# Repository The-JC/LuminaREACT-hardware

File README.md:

# LuminaREACT - Hardware
This repository is the hardware documentation of the LuminaREACT project.

LuminaREACT is CORTEX-M4 based audio visualizer for LED strips using the WS2812 led chip.
For further information visit: [LuminaREACT Firmware](https://lab.katurisoft.com/katurisoft/luminareact/firmware)

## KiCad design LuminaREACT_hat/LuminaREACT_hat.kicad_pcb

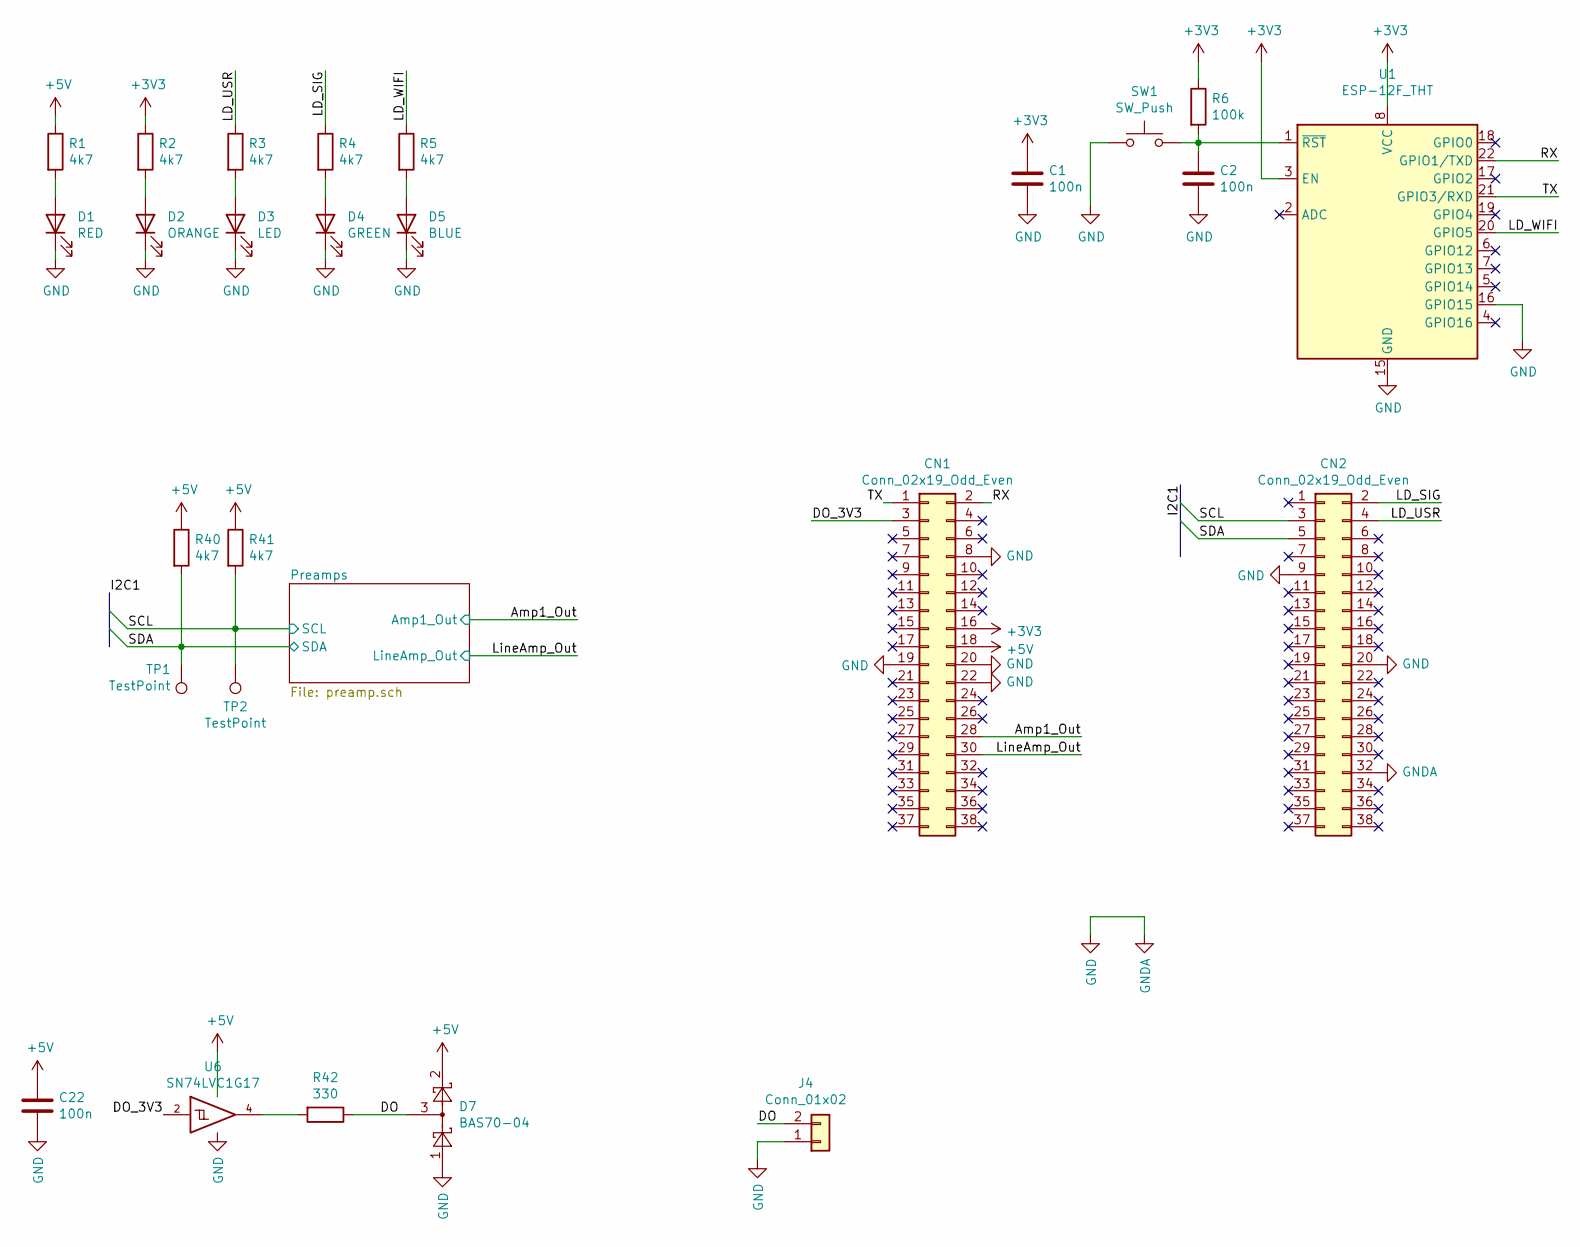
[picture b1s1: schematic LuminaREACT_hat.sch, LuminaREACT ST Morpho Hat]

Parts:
C1, C2, C22: 100n; C_0805_2012Metric
CN1, CN2: Conn_02x19_Odd_Even; PinSocket_2x19_P2.54mm_Vertical
D1: RED; LED_0805_2012Metric
D2: ORANGE; LED_0805_2012Metric
D3: LED; LED_0805_2012Metric
D4: GREEN; LED_0805_2012Metric
D5: BLUE; LED_0805_2012Metric
D7: BAS70-04; SOT-23; LCSC C150242
J4: Conn_01x02; JST_XH_S2B-XH-A-1_1x02_P2.50mm_Horizontal
R1, R2, R3, R4, R5, R40, R41: 4k7; R_0805_2012Metric
R6: 100k; R_0805_2012Metric
R42: 330; R_0805_2012Metric
SW1: SW_Push; SW_SPST_1TS002
TP1, TP2: TestPoint; TestPoint_THTPad_D1.5mm_Drill0.7mm
U1: ESP-12F_THT; ESP-12E-THT
U6: SN74LVC1G17; SOT-23-5_HandSoldering; LCSC C7836

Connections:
+3V3: C1.1, CN1.16, R2.1, R6.1, U1.3 (EN), U1.8 (VCC); also elsewhere on the board
/Amp1_Out: CN1.28; also elsewhere on the board
/DO: D7.3, J4.2, R42.1
/DO_3V3: CN1.3, U6.2
/LD_SIG: CN2.2, R4.1
/LD_USR: CN2.4, R3.1
/LD_WIFI: R5.1, U1.20 (GPIO5)
/LineAmp_Out: CN1.30; also elsewhere on the board
/RX: CN1.2, U1.22 (GPIO1/TXD)
/SCL: CN2.3, R41.2, TP2.1; also elsewhere on the board
/SDA: CN2.5, R40.2, TP1.1; also elsewhere on the board
/TX: CN1.1, U1.21 (GPIO3/RXD)
GND: C1.2, C2.2, C22.2, CN1.8, CN1.19, CN1.20, CN1.22, CN2.9, CN2.20, CN2.32, D1.1 (K), D2.1 (K), D3.1 (K), D4.1 (K), D5.1 (K), D7.1, J4.1, SW1.1, U1.15 (GND), U1.16 (GPIO15), U6.3 (GND); also elsewhere on the board
unnamed: C2.1, R6.2, SW1.2, U1.1 (~RST)
unnamed: D1.2 (A), R1.2
unnamed: D2.2 (A), R2.2
unnamed: D3.2 (A), R3.2
unnamed: D4.2 (A), R4.2
unnamed: D5.2 (A), R5.2
unnamed: R42.2, U6.4

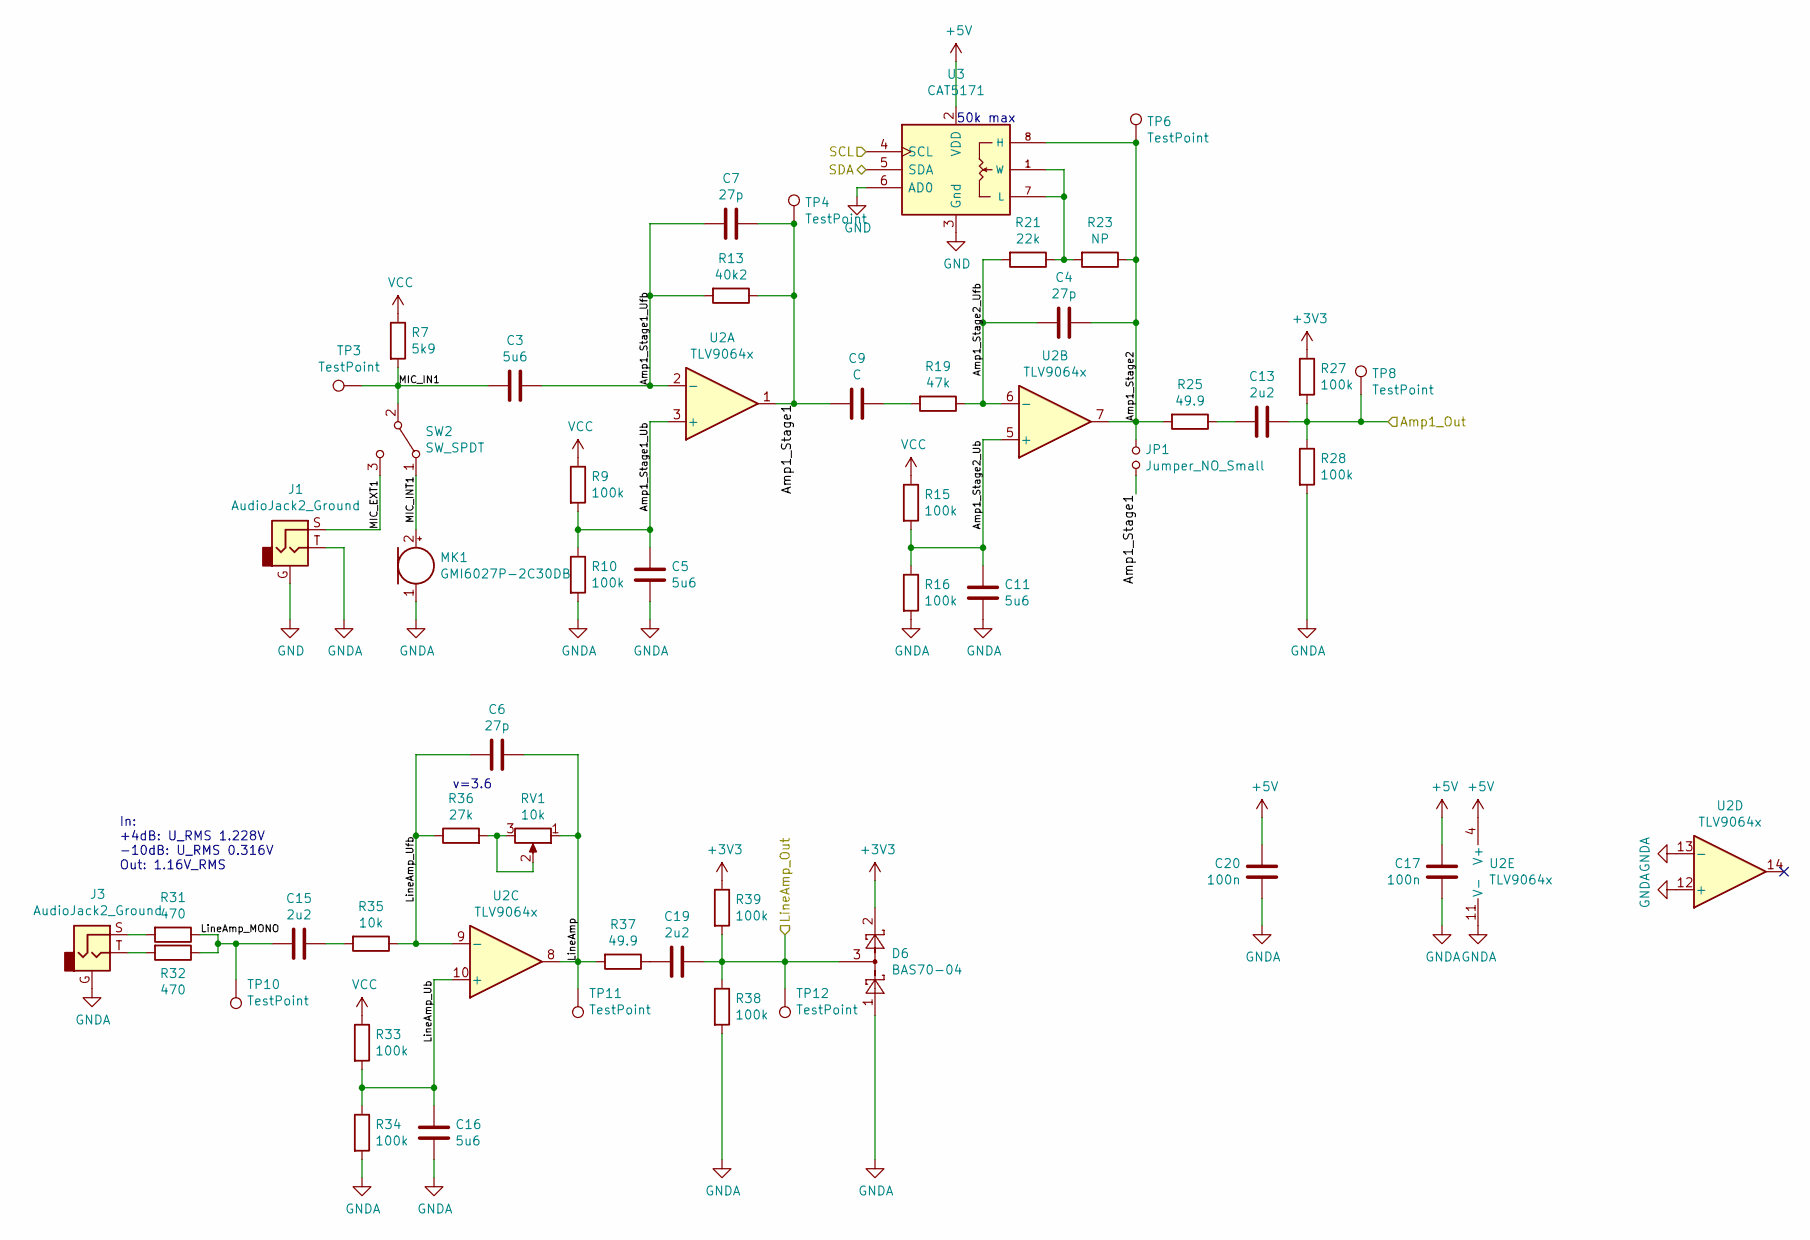
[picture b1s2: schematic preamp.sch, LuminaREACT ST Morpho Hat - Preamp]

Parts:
C3, C5, C11, C16: 5u6; C_0603_1608Metric_Pad1.05x0.95mm_HandSolder
C4, C6, C7: 27p; C_0805_2012Metric
C9: C; C_0805_2012Metric
C13, C15, C19: 2u2; C_0805_2012Metric
C17, C20: 100n; C_0805_2012Metric
D6: BAS70-04; SOT-23; LCSC C150242
J1, J3: AudioJack2_Ground; Jack_3.5mm_BOOMELE_PJ-320B-SMT_Horizontal
JP1: Jumper_NO_Small; SolderJumper-2_P1.3mm_Open_RoundedPad1.0x1.5mm
MK1: GMI6027P-2C30DB; MIC_6.0x2.7MM; LCSC C233898
R7: 5k9; R_0805_2012Metric
R9, R10, R15, R16, R27, R28, R33, R34, R38, R39: 100k; R_0805_2012Metric
R13: 40k2; R_0805_2012Metric
R19: 47k; R_0805_2012Metric
R21: 22k; R_0805_2012Metric
R23: NP; R_0805_2012Metric
R25, R37: 49.9; R_0805_2012Metric
R31, R32: 470; R_0805_2012Metric
R35: 10k; R_0805_2012Metric
R36: 27k; R_0805_2012Metric
RV1: 10k; Potentiometer_Bourns_3296W_Vertical
SW2: SW_SPDT; SW_SPDT_SK-3390
TP3, TP4, TP6, TP8, TP10, TP11, TP12: TestPoint; TestPoint_THTPad_D1.5mm_Drill0.7mm
U2: TLV9064x; SO-14_3.9x8.65mm_P1.27mm; LCSC C388176
U3: CAT5171; SOT-23-8_Handsoldering; LCSC C154777

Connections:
+3V3: D6.2, R27.1, R39.1; also elsewhere on the board
/Amp1_Out: C13.1, R27.2, R28.1, TP8.1; also elsewhere on the board
/LineAmp_Out: C19.1, D6.3, R38.1, R39.2, TP12.1; also elsewhere on the board
/Preamps/Amp1_Stage1: C7.1, C9.2, JP1.1, R13.1, TP4.1, U2.1
/Preamps/Amp1_Stage1_Ub: C5.1, R9.2, R10.1, U2.3 (+)
/Preamps/Amp1_Stage1_Ufb: C3.1, C7.2, R13.2, U2.2 (-)
/Preamps/Amp1_Stage2: C4.1, JP1.2, R23.1, R25.2, TP6.1, U2.7, U3.8 (H)
/Preamps/Amp1_Stage2_Ub: C11.1, R15.2, R16.1, U2.5 (+)
/Preamps/Amp1_Stage2_Ufb: C4.2, R19.1, R21.2, U2.6 (-)
/Preamps/LineAmp: C6.1, R37.2, RV1.1, TP11.1, U2.8
/Preamps/LineAmp_MONO: C15.2, R31.1, R32.1, TP10.1
/Preamps/LineAmp_Ub: C16.1, R33.2, R34.1, U2.10 (+)
/Preamps/LineAmp_Ufb: C6.2, R35.1, R36.1, U2.9 (-)
/Preamps/MIC_EXT1: J1.S, SW2.3 (C)
/Preamps/MIC_IN1: C3.2, R7.2, SW2.2 (B), TP3.1
/Preamps/MIC_INT1: MK1.2 (+), SW2.1 (A)
/SCL: U3.4 (SCL); also elsewhere on the board
/SDA: U3.5 (SDA); also elsewhere on the board
GND: C5.2, C11.2, C16.2, C17.2, C20.2, D6.1, J1.G, J1.T, J3.G, MK1.1 (-), R10.2, R16.2, R28.2, R34.2, R38.2, U2.11 (V-), U2.12 (+), U2.13 (-), U3.3 (Gnd), U3.6 (AD0); also elsewhere on the board
unnamed: C9.1, R19.2
unnamed: C13.2, R25.1
unnamed: C15.1, R35.2
unnamed: C19.2, R37.1
unnamed: J3.S, R31.2
unnamed: J3.T, R32.2
unnamed: R21.1, R23.2, U3.1 (W), U3.7 (L)
unnamed: R36.2, RV1.2, RV1.3

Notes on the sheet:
50k max
v=3.6
In: +4dB: U_RMS 1.228V -10dB: U_RMS 0.316V Out: 1.16V_RMS

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
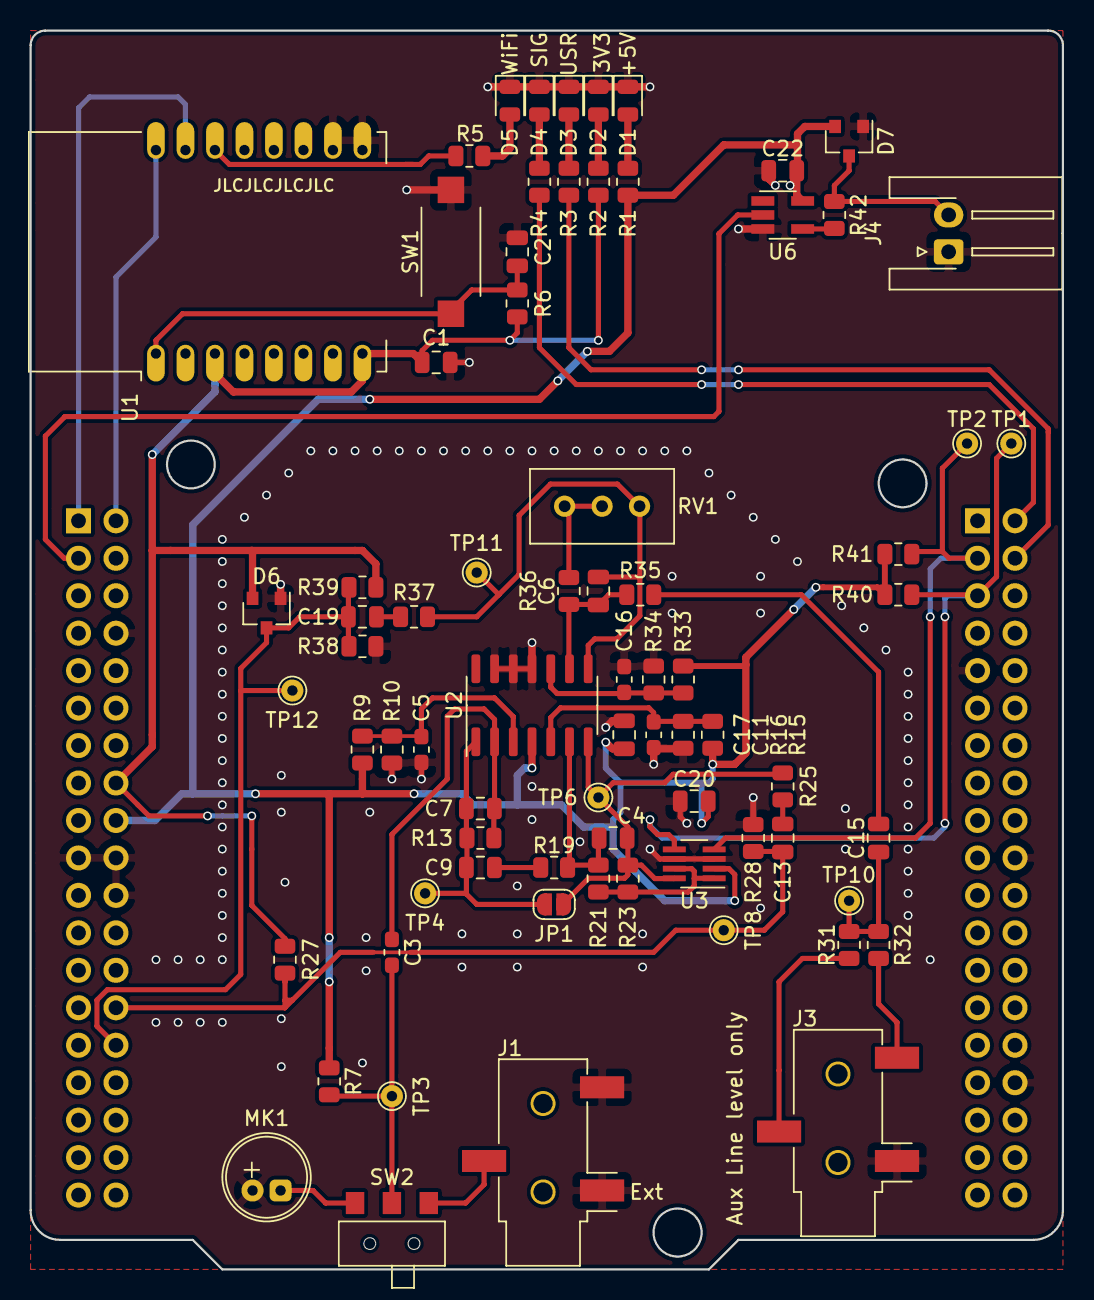
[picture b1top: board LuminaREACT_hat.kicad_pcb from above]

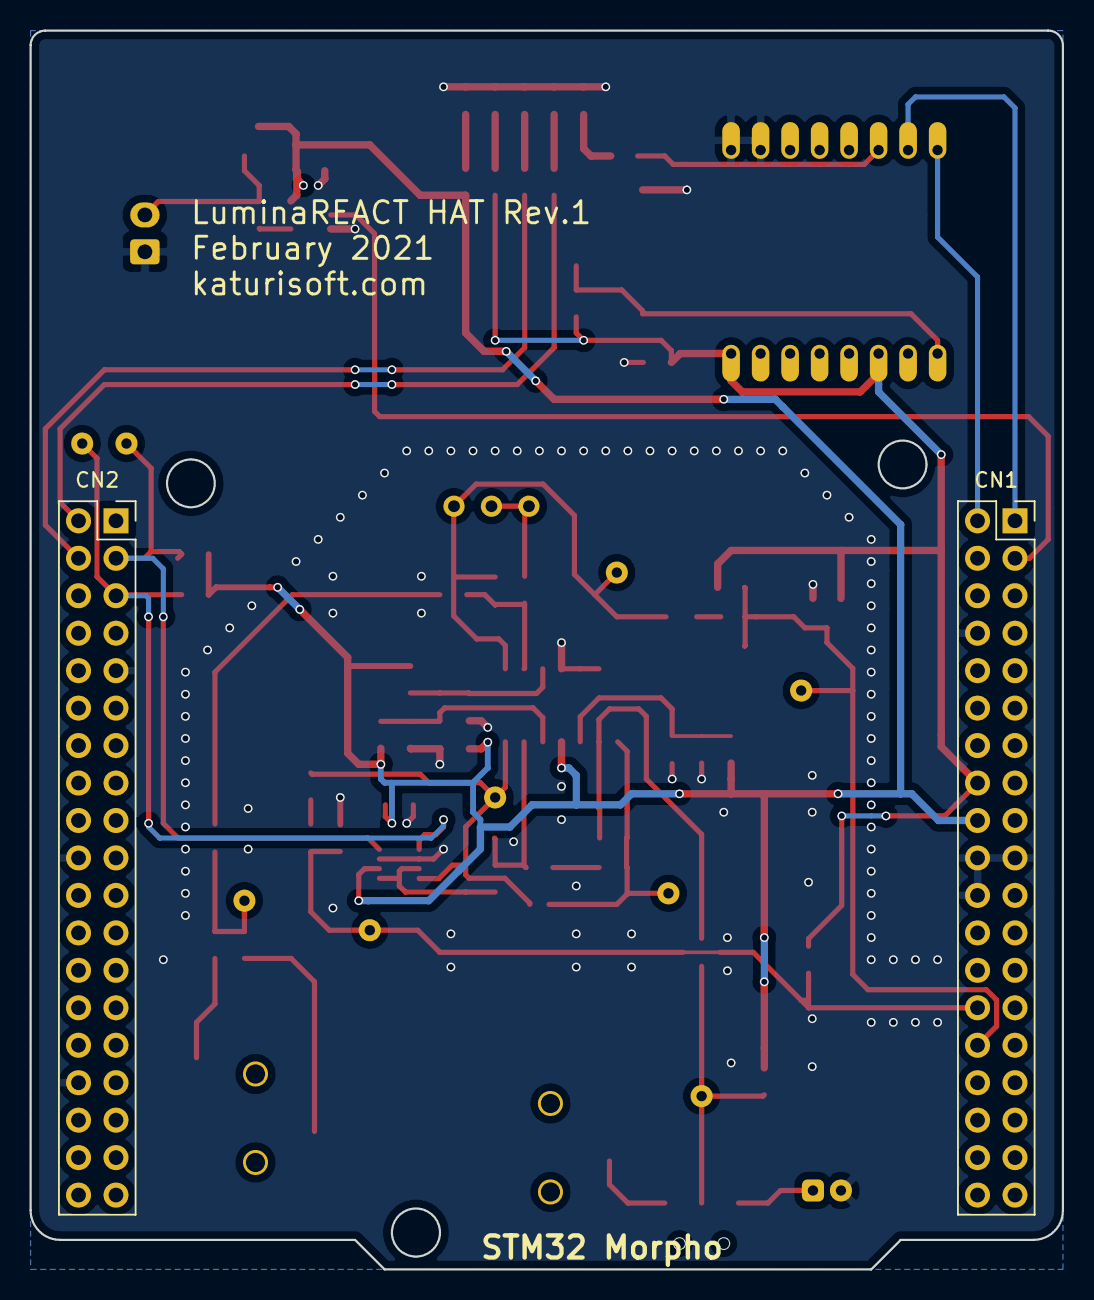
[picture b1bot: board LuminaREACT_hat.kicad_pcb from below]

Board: 2 copper layers, 70.0 x 84.0 mm, 76 parts (2 on the bottom side), 42 nets.
